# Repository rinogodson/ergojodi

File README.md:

---
### Fully custom hot-swappable split mechanical keyboard that features a very ergonomic layout and uses USB-C for everything, way better than accident-friendly TRRS. Runs on QMK software, controlling key functions. The fully assembled keyboard's 3D Model's STEP file is over 100MB, So, you can find the drive link in `assembly.md`
The name comes from two words, "Ergo" meaning Ergonomics, and "Jodi" meaning pair.

> **Why I built this**: I needed an ergonomic keyboard to use with my machines that suits my ergonomics. I aligned and laid out the keys to match my finger heights.

---

### Schematic
Ergogen keebs doesn't need a schematic, because it is in ergogen... But, for your sake, I made one!

---
### PCB
Designed in Ergogen and Routed in KiCad

---
## Case  
Case designed with ergogen. It comes in two parts: the top plate and bottom case. The M2 Screw holes are already present, and heat inserts should be added to the top plate.

---
## Firmware  
This Keyboard runs on QMK software; the uf2 file to flash can be found in `firmware/uf2`.  

## Parts List and Links:
| Name | Price (USD) | Quantity | Link | Total (USD) | Delivery and Tax | Shop Total (USD) |
| :--- | :--- | :--- | :--- | :--- | :--- | :--- |
| Outemu Mechanical Switches for Swappable Keyboards (Pack of 20) | $2.30 | 2 | [Visit Shop](https://www.thecosmicbyte.com/product/outemu-mechanical-switches-for-swappable-keyboards-pack-of-20/?attribute_pa_switch-type=prelubed-brown-switch) | $4.60 | $0.87 | $5.46 |
| Gateron Hotswap Sockets | $0.10 | 40 | [Visit Shop](https://stackskb.com/store/gateron-hotswap-sockets/) | $4.18 | $1.36 | $5.54 |
| Blank DSA Keycaps (1u) (5n per order) | $0.99 | 8 | [Visit Shop](https://meckeys.com/shop/accessories/keyboard-accessories/keycaps/blank/blank-dsa-keycaps-1u/) | $7.94 | $1.04 | $8.98 |
| TYPE-C-31-M-12-Hroparts-5A 1 16P Female Type-C SMD USB Connectors ROHS | $0.40 | 2 | [Visit Shop](https://robu.in/product/type-c-31-m-12-hroparts-5a-1-16p-female-type-c-smd-usb-connectors-rohs/) | $0.79 | Free | $14.33 |
| Seeed Studio XIAO RP2040 v1.0 | $6.46 | 2 | [Visit Shop](https://robu.in/product/seeed-studio-xiao-rp2040-v1-0/) | $12.91 | | |
| 1N4148-T50A-Onsemi-100V 1V@10mA 4ns 200mA DO-35 Switching Diodes ROHS | $0.06 | 10 | [Visit Shop](https://robu.in/product/1n4148-t50a-onsemi-100v-1v10ma-4ns-200ma-do-35-switching-diodes-rohs/) | $0.63 | | |
| M2 X 3mm Brass Threaded Inserts (Dia. 2mm, Length 3mm) | $0.02 | 15 | [Visit Shop](https://onlyscrews.in/products/m2-x-3mm-brass-threaded-inserts?variant=49728872448313) | $0.28 | $0.73 | $1.70 |
| M2 X 8mm Phillips Round head Laptop Screw (Dia. 2mm, Length 8mm) | $0.05 | 15 | [Visit Shop](https://onlyscrews.in/products/m2-x-8mm-phillips-round-head-laptop-screw-1?variant=49693360423225) | $0.69 | | |
| PCB Manufacturing & Shipping (JLCPCB) | $26.17 | 1 | [Visit Shop](https://jlcpcb.com/) | $26.17 | - | $26.17 |
| 3D Printing & Shipping (3Ding) | $11.43 | 1 | [Visit Shop](https://3ding.in/) | $11.43 | - | $11.43 |

### Total ~ $74

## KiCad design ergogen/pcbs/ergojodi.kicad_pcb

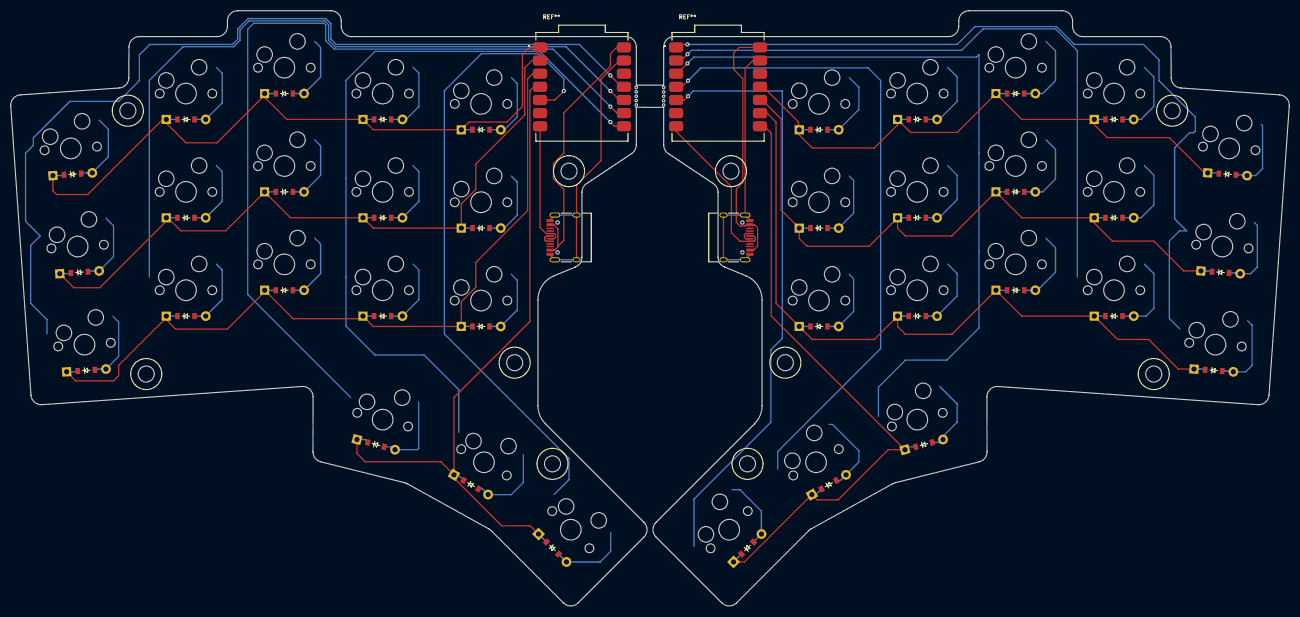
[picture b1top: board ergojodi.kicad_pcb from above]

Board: 2 copper layers, 247.0 x 115.0 mm, 74 parts (0 on the bottom side), 62 nets.

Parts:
D1, D2, D3, D4, D5, D6, D7, D8, D9, D10, D11, D12, D13, D14, D15, D16, D17, D18, D19, D20, D21, D22, D23, D24, D25, D26, D27, D28, D29, D30, D31, D32, D33, D34, D35, D36: ComboDiode
S1, S2, S3, S4, S5, S6, S7, S8, S9, S10, S11, S12, S13, S14, S15, S16, S17, S18, S19, S20, S21, S22, S23, S24, S25, S26, S27, S28, S29, S30, S31, S32, S33, S34, S35, S36: MX
XX2, XX3: USB_C_Receptacle_HRO_TYPE-C-31-M-12

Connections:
far_thumb: D18.2, S18.2
home_thumb: D17.2, S17.2
index_bottom: D10.2, S10.2
index_home: D11.2, S11.2
index_top: D12.2, S12.2
inner_bottom: D13.2, S13.2
inner_home: D14.2, S14.2
inner_top: D15.2, S15.2
l_A0: D3.1, D6.1, D9.1, D12.1, D15.1
l_A1: D2.1, D5.1, D8.1, D11.1, D14.1
l_A2: D1.1, D4.1, D7.1, D10.1, D13.1
l_A3: D16.1, D17.1, D18.1
l_A4: S13.1, S14.1, S15.1, S18.1
l_A7: S10.1, S11.1, S12.1, S17.1
l_A8: S7.1, S8.1, S9.1, S16.1
l_A9: S4.1, S5.1, S6.1
l_A10: S1.1, S2.1, S3.1
l_Dminus: XX2.A7, XX2.B7
l_Dplus: XX2.A6, XX2.B6
l_GND: XX2.A1, XX2.A12, XX2.B1, XX2.B12, XX2.NP
l_VCC: XX2.A4, XX2.A9, XX2.B4, XX2.B9
middle_bottom: D7.2, S7.2
middle_home: D8.2, S8.2
middle_top: D9.2, S9.2
mirror_far_thumb: D36.2, S36.2
mirror_home_thumb: D35.2, S35.2
mirror_index_bottom: D28.2, S28.2
mirror_index_home: D29.2, S29.2
mirror_index_top: D30.2, S30.2
mirror_inner_bottom: D31.2, S31.2
mirror_inner_home: D32.2, S32.2
mirror_inner_top: D33.2, S33.2
mirror_middle_bottom: D25.2, S25.2
mirror_middle_home: D26.2, S26.2
mirror_middle_top: D27.2, S27.2
mirror_near_thumb: D34.2, S34.2
mirror_pinky_bottom: D19.2, S19.2
mirror_pinky_home: D20.2, S20.2
mirror_pinky_top: D21.2, S21.2
mirror_ring_bottom: D22.2, S22.2
mirror_ring_home: D23.2, S23.2
mirror_ring_top: D24.2, S24.2
near_thumb: D16.2, S16.2
pinky_bottom: D1.2, S1.2
pinky_home: D2.2, S2.2
pinky_top: D3.2, S3.2
r_A0: S19.1, S20.1, S21.1
r_A1: S22.1, S23.1, S24.1
r_A2: S25.1, S26.1, S27.1, S34.1
r_A3: S28.1, S29.1, S30.1, S35.1
r_A4: S31.1, S32.1, S33.1, S36.1
r_A7: D34.1, D35.1, D36.1
r_A8: D19.1, D22.1, D25.1, D28.1, D31.1
r_A9: D20.1, D23.1, D26.1, D29.1, D32.1
r_A10: D21.1, D24.1, D27.1, D30.1, D33.1
r_Dminus: XX3.A7, XX3.B7
r_Dplus: XX3.A6, XX3.B6
r_GND: XX3.A1, XX3.A12, XX3.B1, XX3.B12, XX3.NP
r_VCC: XX3.A4, XX3.A9, XX3.B4, XX3.B9
ring_bottom: D4.2, S4.2
ring_home: D5.2, S5.2
ring_top: D6.2, S6.2
